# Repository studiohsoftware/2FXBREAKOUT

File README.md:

# 2FXBREAKOUT
# Effects Breakout 

Attach this daughterboard to your 206e/207e for up to four send/return channels.
</br>
</br>

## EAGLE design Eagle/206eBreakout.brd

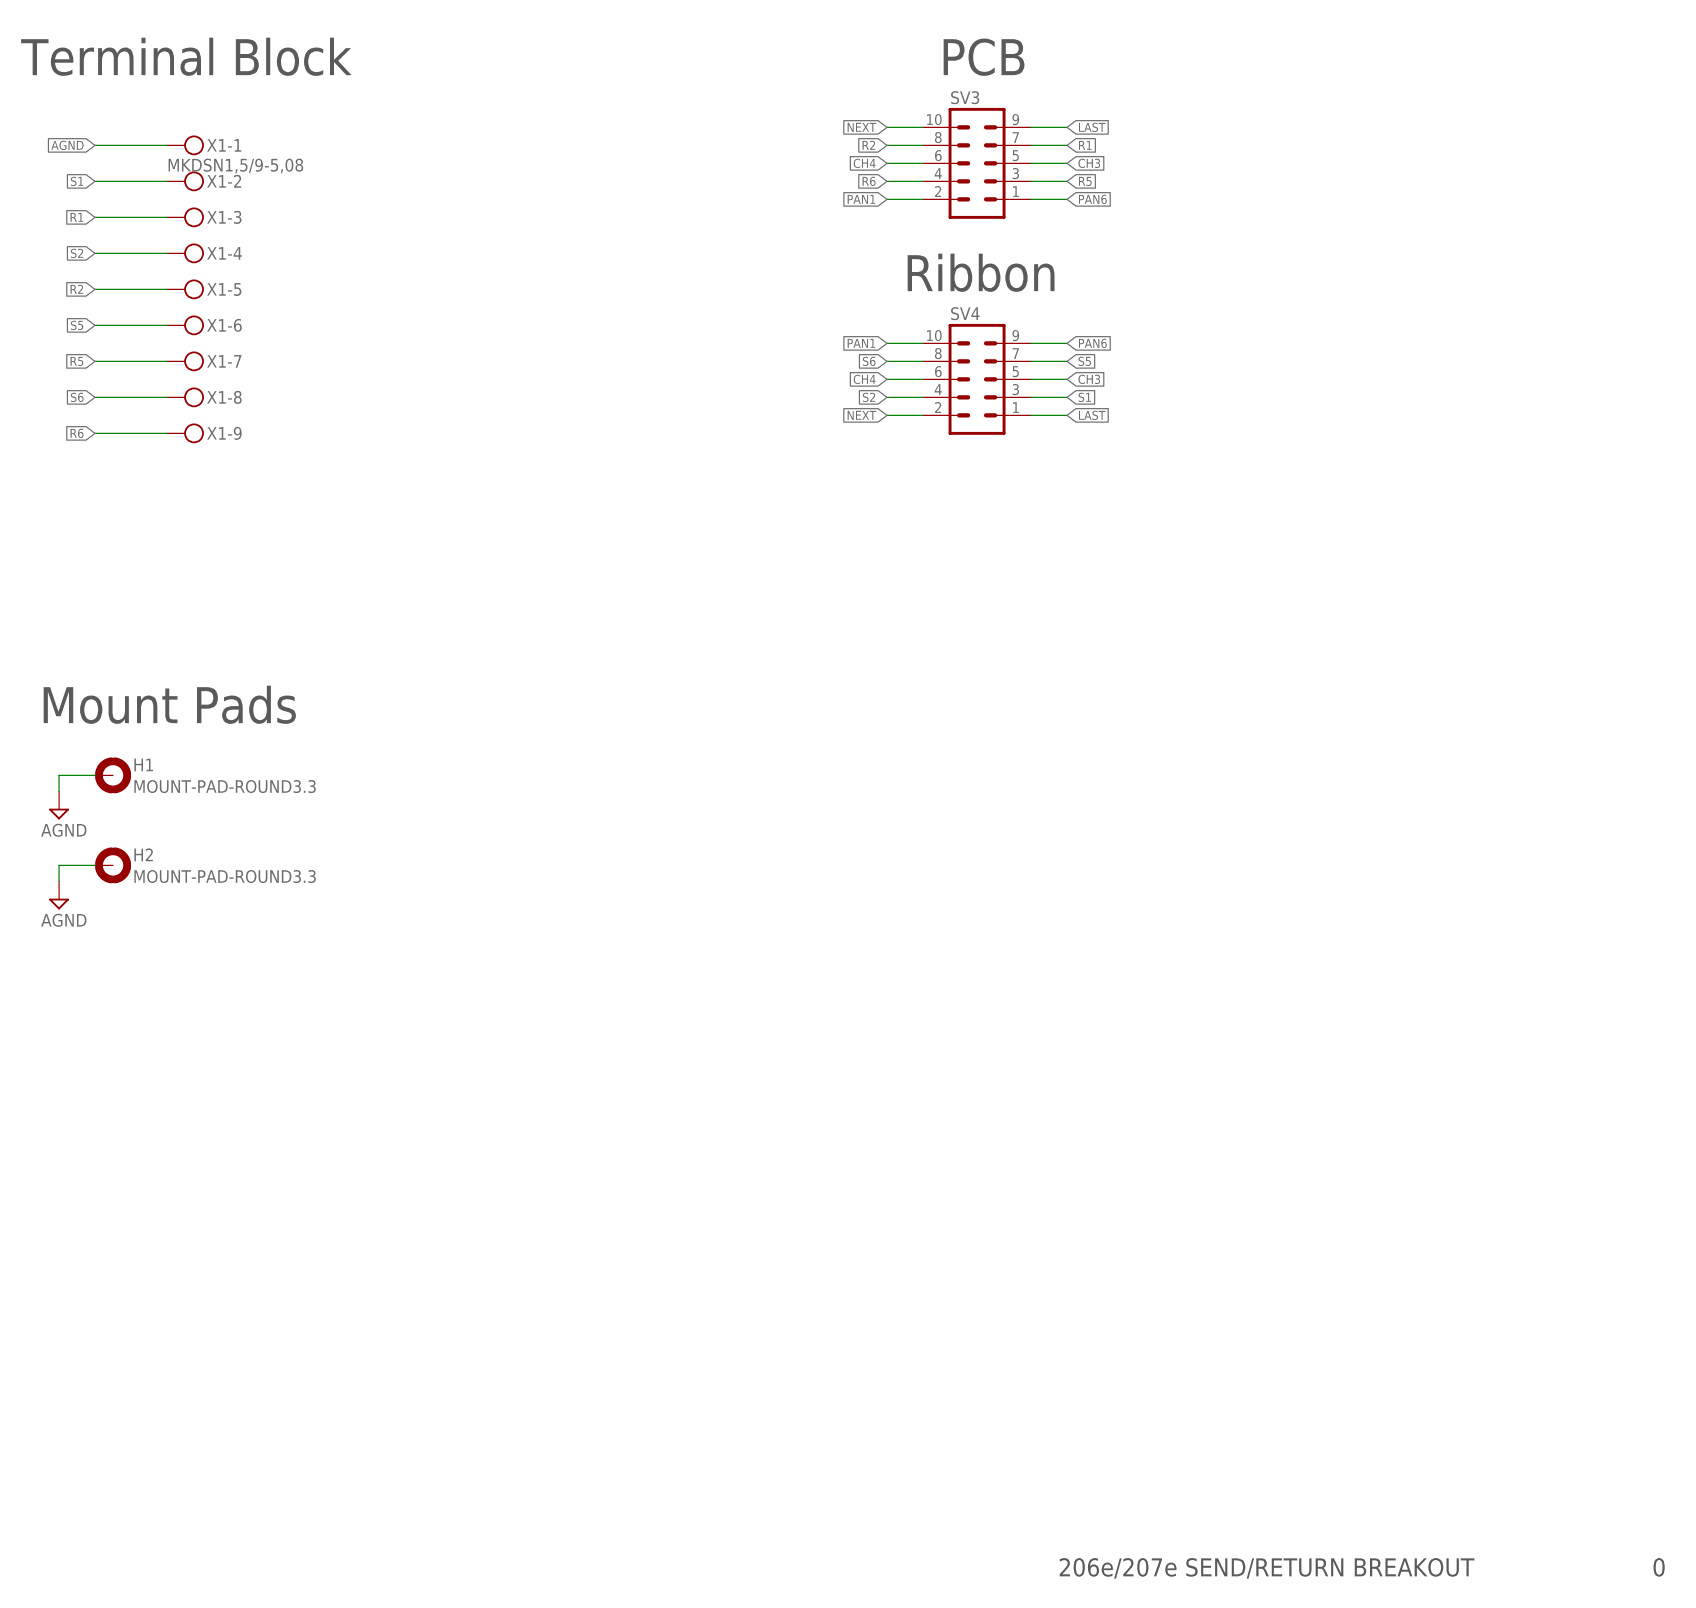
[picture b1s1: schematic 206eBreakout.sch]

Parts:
H1, H2: MOUNT-PAD-ROUND3.3; 3,3-PAD
SV3, SV4: MA05-2
X1: MKDSN1,5/9-5,08

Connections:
AGND: H1.B3,3, H2.B3,3, X1.1
CH3: SV3.5, SV4.5
CH4: SV3.6, SV4.6
LAST: SV3.9, SV4.1
NEXT: SV3.10, SV4.2
PAN1: SV3.2, SV4.10
PAN6: SV3.1, SV4.9
R1: SV3.7, X1.3
R2: SV3.8, X1.5
R5: SV3.3, X1.7
R6: SV3.4, X1.9
S1: SV4.3, X1.2
S2: SV4.4, X1.4
S5: SV4.7, X1.6
S6: SV4.8, X1.8

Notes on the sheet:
206e/207e SEND/RETURN BREAKOUT
Mount Pads
PCB
Ribbon
Terminal Block

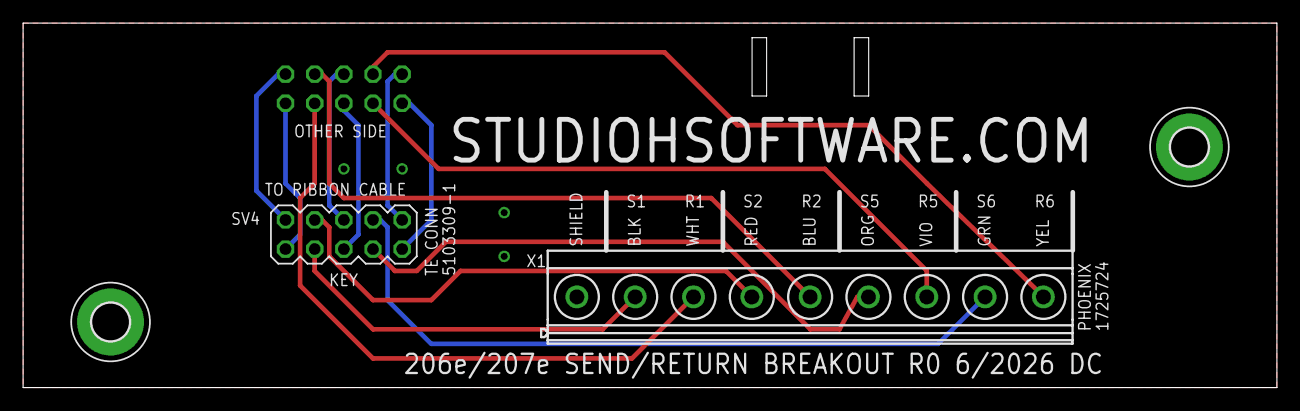
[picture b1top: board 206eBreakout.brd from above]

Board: 2 copper layers, 109.2 x 31.7 mm, 5 parts (1 on the bottom side), 15 nets.
